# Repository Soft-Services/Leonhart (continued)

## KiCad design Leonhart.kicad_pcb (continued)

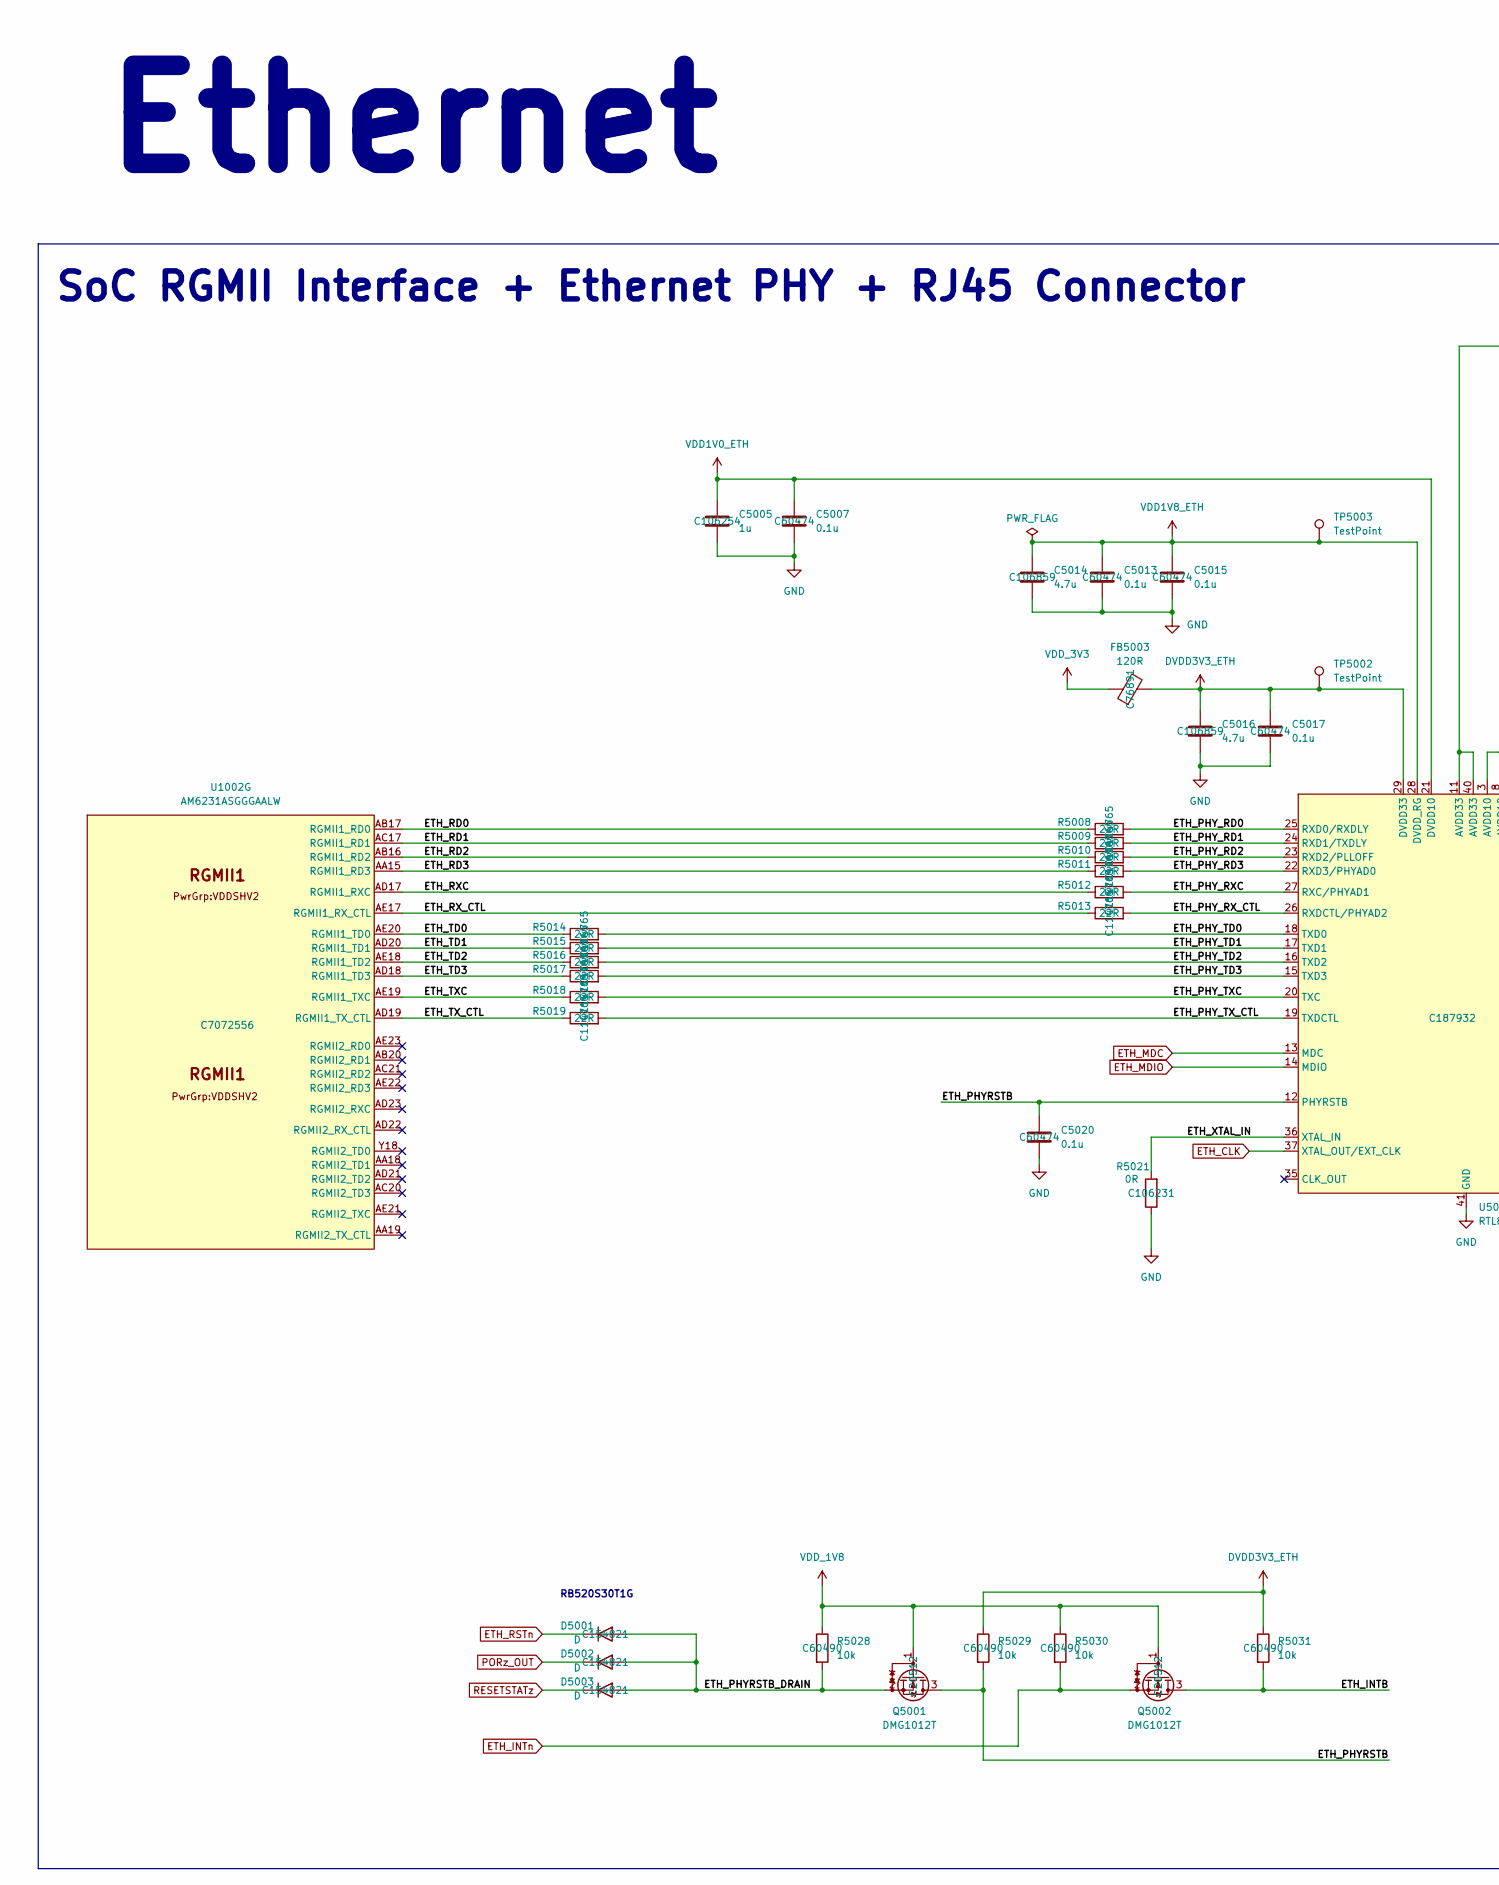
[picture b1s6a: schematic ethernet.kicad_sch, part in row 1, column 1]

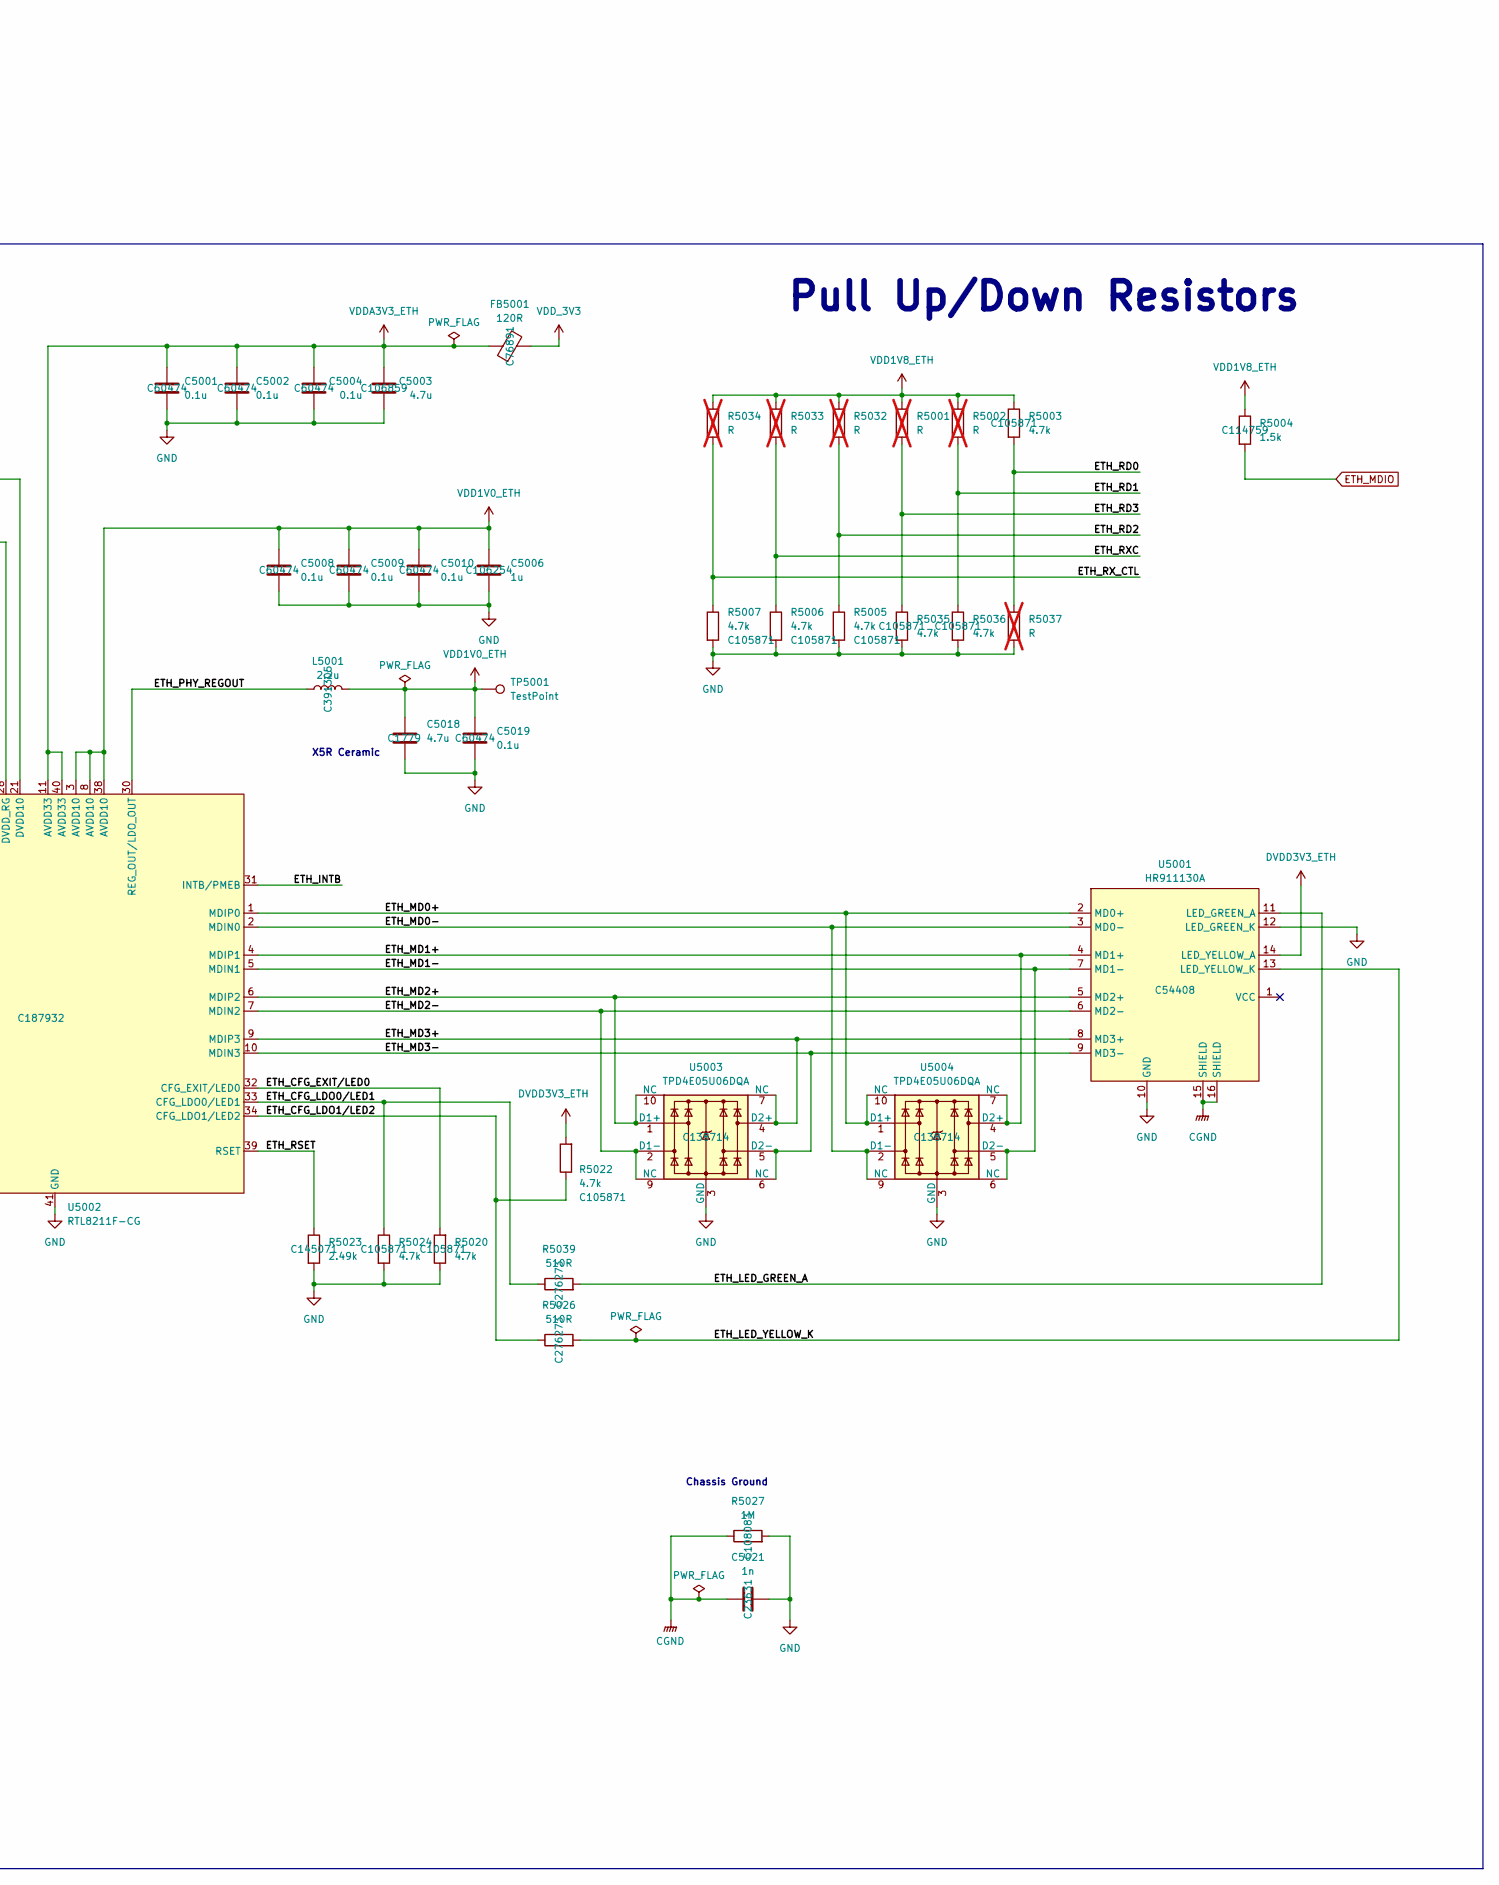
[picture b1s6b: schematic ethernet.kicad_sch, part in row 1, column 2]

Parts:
C5001, C5002, C5004, C5007, C5008, C5009, C5010, C5013, C5015, C5017, C5019, C5020: 0.1u; C_0402_1005Metric; JLCPCB Part# C60474
C5003, C5014, C5016: 4.7u; C_0402_1005Metric; JLCPCB Part# C106859
C5005, C5006: 1u; C_0402_1005Metric; JLCPCB Part# C106254
C5018: 4.7u; C_0805_2012Metric; JLCPCB Part# C1779
C5021: 1n; C_1206_3216Metric; JLCPCB Part# C23631
D5001, D5002, D5003: D; D_SOD-523; JLCPCB Part# C154821
FB5001, FB5003: 120R; R_0402_1005Metric; JLCPCB Part# C76891
L5001: 2.2u; DFE2HCAH1R0MJ0L; JLCPCB Part# C391305
Q5001, Q5002: DMG1012T; SOT-523; JLCPCB Part# C20512
R5001, R5002, R5032, R5033, R5034, R5037: R; R_0402_1005Metric; not fitted
R5003, R5005, R5006, R5007, R5020, R5022, R5024, R5035, R5036: 4.7k; R_0402_1005Metric; JLCPCB Part# C105871
R5004: 1.5k; R_0402_1005Metric; JLCPCB Part# C114759
R5008, R5009, R5010, R5011, R5012, R5013, R5014, R5015, R5016, R5017, R5018, R5019: 22R; R_0402_1005Metric; JLCPCB Part# C114765
R5021: 0R; R_0402_1005Metric; JLCPCB Part# C106231
R5023: 2.49k; R_0402_1005Metric; JLCPCB Part# C145071
R5026, R5039: 510R; R_0402_1005Metric; JLCPCB Part# C276273
R5027: 1M; R_0402_1005Metric; JLCPCB Part# C108083
R5028, R5029, R5030, R5031: 10k; R_0402_1005Metric; JLCPCB Part# C60490
TP5001, TP5002, TP5003: TestPoint; TestPoint_Pad_1.0x1.0mm
U1002: AM6231ASGGGAALW; BGA425C50P25X25_1300X1300X89; JLCPCB Part# C7072556
U5001: HR911130A; JLCPCB Part# C54408
U5002: RTL8211F-CG; QFN-40-1EP_5x5mm_P0.4mm_EP3.6x3.6mm; JLCPCB Part# C187932
U5003, U5004: TPD4E05U06DQA; USON-10_2.5x1.0mm_P0.5mm; JLCPCB Part# C138714

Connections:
/Ethernet [5]/ETH_CFG_EXIT/LED0: R5020.2, U5002.32 (CFG_EXIT/LED0)
/Ethernet [5]/ETH_CFG_LDO0/LED1: R5024.1, R5039.1, U5002.33 (CFG_LDO0/LED1)
/Ethernet [5]/ETH_CFG_LDO1/LED2: R5022.1, R5026.1, U5002.34 (CFG_LDO1/LED2)
/Ethernet [5]/ETH_INTB: Q5002.3 (D), R5031.2, U5002.31 (INTB/PMEB)
/Ethernet [5]/ETH_LED_GREEN_A: R5039.2, U5001.11 (LED_GREEN_A)
/Ethernet [5]/ETH_LED_YELLOW_K: R5026.2, U5001.13 (LED_YELLOW_K)
/Ethernet [5]/ETH_MD0+: U5001.2 (MD0+), U5002.1 (MDIP0), U5004.1 (D1+), U5004.10 (NC)
/Ethernet [5]/ETH_MD0-: U5001.3 (MD0-), U5002.2 (MDIN0), U5004.2 (D1-), U5004.9 (NC)
/Ethernet [5]/ETH_MD1+: U5001.4 (MD1+), U5002.4 (MDIP1), U5004.4 (D2+), U5004.7 (NC)
/Ethernet [5]/ETH_MD1-: U5001.7 (MD1-), U5002.5 (MDIN1), U5004.5 (D2-), U5004.6 (NC)
/Ethernet [5]/ETH_MD2+: U5001.5 (MD2+), U5002.6 (MDIP2), U5003.1 (D1+), U5003.10 (NC)
/Ethernet [5]/ETH_MD2-: U5001.6 (MD2-), U5002.7 (MDIN2), U5003.2 (D1-), U5003.9 (NC)
/Ethernet [5]/ETH_MD3+: U5001.8 (MD3+), U5002.9 (MDIP3), U5003.4 (D2+), U5003.7 (NC)
/Ethernet [5]/ETH_MD3-: U5001.9 (MD3-), U5002.10 (MDIN3), U5003.5 (D2-), U5003.6 (NC)
/Ethernet [5]/ETH_PHYRSTB: C5020.1, Q5001.3 (D), R5029.2, U5002.12 (PHYRSTB)
/Ethernet [5]/ETH_PHYRSTB_DRAIN: D5001.2 (A), D5002.2 (A), D5003.2 (A), Q5001.2 (S), R5028.2
/Ethernet [5]/ETH_PHY_RD0: R5008.2, U5002.25 (RXD0/RXDLY)
/Ethernet [5]/ETH_PHY_RD1: R5009.2, U5002.24 (RXD1/TXDLY)
/Ethernet [5]/ETH_PHY_RD2: R5010.2, U5002.23 (RXD2/PLLOFF)
/Ethernet [5]/ETH_PHY_RD3: R5011.2, U5002.22 (RXD3/PHYAD0)
/Ethernet [5]/ETH_PHY_REGOUT: L5001.1, U5002.30 (REG_OUT/LDO_OUT)
/Ethernet [5]/ETH_PHY_RXC: R5012.2, U5002.27 (RXC/PHYAD1)
/Ethernet [5]/ETH_PHY_RX_CTL: R5013.2, U5002.26 (RXDCTL/PHYAD2)
/Ethernet [5]/ETH_PHY_TD0: R5014.2, U5002.18 (TXD0)
/Ethernet [5]/ETH_PHY_TD1: R5015.2, U5002.17 (TXD1)
/Ethernet [5]/ETH_PHY_TD2: R5016.2, U5002.16 (TXD2)
/Ethernet [5]/ETH_PHY_TD3: R5017.2, U5002.15 (TXD3)
/Ethernet [5]/ETH_PHY_TXC: R5018.2, U5002.20 (TXC)
/Ethernet [5]/ETH_PHY_TX_CTL: R5019.2, U5002.19 (TXDCTL)
/Ethernet [5]/ETH_RD0: R5003.2, R5008.1, R5037.1, U1002.AB17 (RGMII1_RD0)
/Ethernet [5]/ETH_RD1: R5002.2, R5009.1, R5036.1, U1002.AC17 (RGMII1_RD1)
/Ethernet [5]/ETH_RD2: R5005.1, R5010.1, R5032.2, U1002.AB16 (RGMII1_RD2)
/Ethernet [5]/ETH_RD3: R5001.2, R5011.1, R5035.1, U1002.AA15 (RGMII1_RD3)
/Ethernet [5]/ETH_RSET: R5023.1, U5002.39 (RSET)
/Ethernet [5]/ETH_RXC: R5006.1, R5012.1, R5033.2, U1002.AD17 (RGMII1_RXC)
/Ethernet [5]/ETH_RX_CTL: R5007.1, R5013.1, R5034.2, U1002.AE17 (RGMII1_RX_CTL)
/Ethernet [5]/ETH_TD0: R5014.1, U1002.AE20 (RGMII1_TD0)
/Ethernet [5]/ETH_TD1: R5015.1, U1002.AD20 (RGMII1_TD1)
/Ethernet [5]/ETH_TD2: R5016.1, U1002.AE18 (RGMII1_TD2)
/Ethernet [5]/ETH_TD3: R5017.1, U1002.AD18 (RGMII1_TD3)
/Ethernet [5]/ETH_TXC: R5018.1, U1002.AE19 (RGMII1_TXC)
/Ethernet [5]/ETH_TX_CTL: R5019.1, U1002.AD19 (RGMII1_TX_CTL)
/Ethernet [5]/ETH_XTAL_IN: R5021.2, U5002.36 (XTAL_IN)
CGND: C5021.1, R5027.1, U5001.15 (SHIELD), U5001.16 (SHIELD)
DVDD3V3_ETH: C5016.1, C5017.1, FB5003.2, R5022.2, R5029.1, R5031.1, TP5002.1, U5001.14 (LED_YELLOW_A), U5002.29 (DVDD33); also elsewhere on the board
ETH_CLK: U5002.37 (XTAL_OUT/EXT_CLK); also elsewhere on the board
ETH_INTn: Q5002.2 (S), R5030.2; also elsewhere on the board
ETH_MDC: U5002.13 (MDC); also elsewhere on the board
ETH_MDIO: R5004.2, U5002.14 (MDIO); also elsewhere on the board
ETH_RSTn: D5001.1 (K); also elsewhere on the board
GND: C5001.2, C5002.2, C5003.2, C5004.2, C5005.2, C5006.2, C5007.2, C5008.2, C5009.2, C5010.2, C5013.2, C5014.2, C5015.2, C5016.2, C5017.2, C5018.2, C5019.2, C5020.2, C5021.2, R5005.2, R5006.2, R5007.2, R5020.1, R5021.1, R5023.2, R5024.2, R5027.2, R5035.2, R5036.2, R5037.2, U5001.10 (GND), U5001.12 (LED_GREEN_K), U5002.41 (GND), U5003.3 (GND), U5003.8 (GND), U5004.3 (GND), U5004.8 (GND); also elsewhere on the board
PORz_OUT: D5002.1 (K); also elsewhere on the board
RESETSTATz: D5003.1 (K); also elsewhere on the board
VDD1V0_ETH: C5005.1, C5006.1, C5007.1, C5008.1, C5009.1, C5010.1, C5018.1, C5019.1, L5001.2, TP5001.1, U5002.3 (AVDD10), U5002.8 (AVDD10), U5002.21 (DVDD10), U5002.38 (AVDD10); also elsewhere on the board
VDD1V8_ETH: C5013.1, C5014.1, C5015.1, R5001.1, R5002.1, R5003.1, R5004.1, R5032.1, R5033.1, R5034.1, TP5003.1, U5002.28 (DVDD_RG); also elsewhere on the board
VDDA3V3_ETH: C5001.1, C5002.1, C5003.1, C5004.1, FB5001.1, U5002.11 (AVDD33), U5002.40 (AVDD33)
VDD_1V8: Q5001.1 (G), Q5002.1 (G), R5028.1, R5030.1; also elsewhere on the board
VDD_3V3: FB5001.2, FB5003.1; also elsewhere on the board

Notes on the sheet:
X5R Ceramic
Pull Up/Down Resistors
RB520S30T1G
SoC RGMII Interface + Ethernet PHY + RJ45 Connector
Chassis Ground
Ethernet

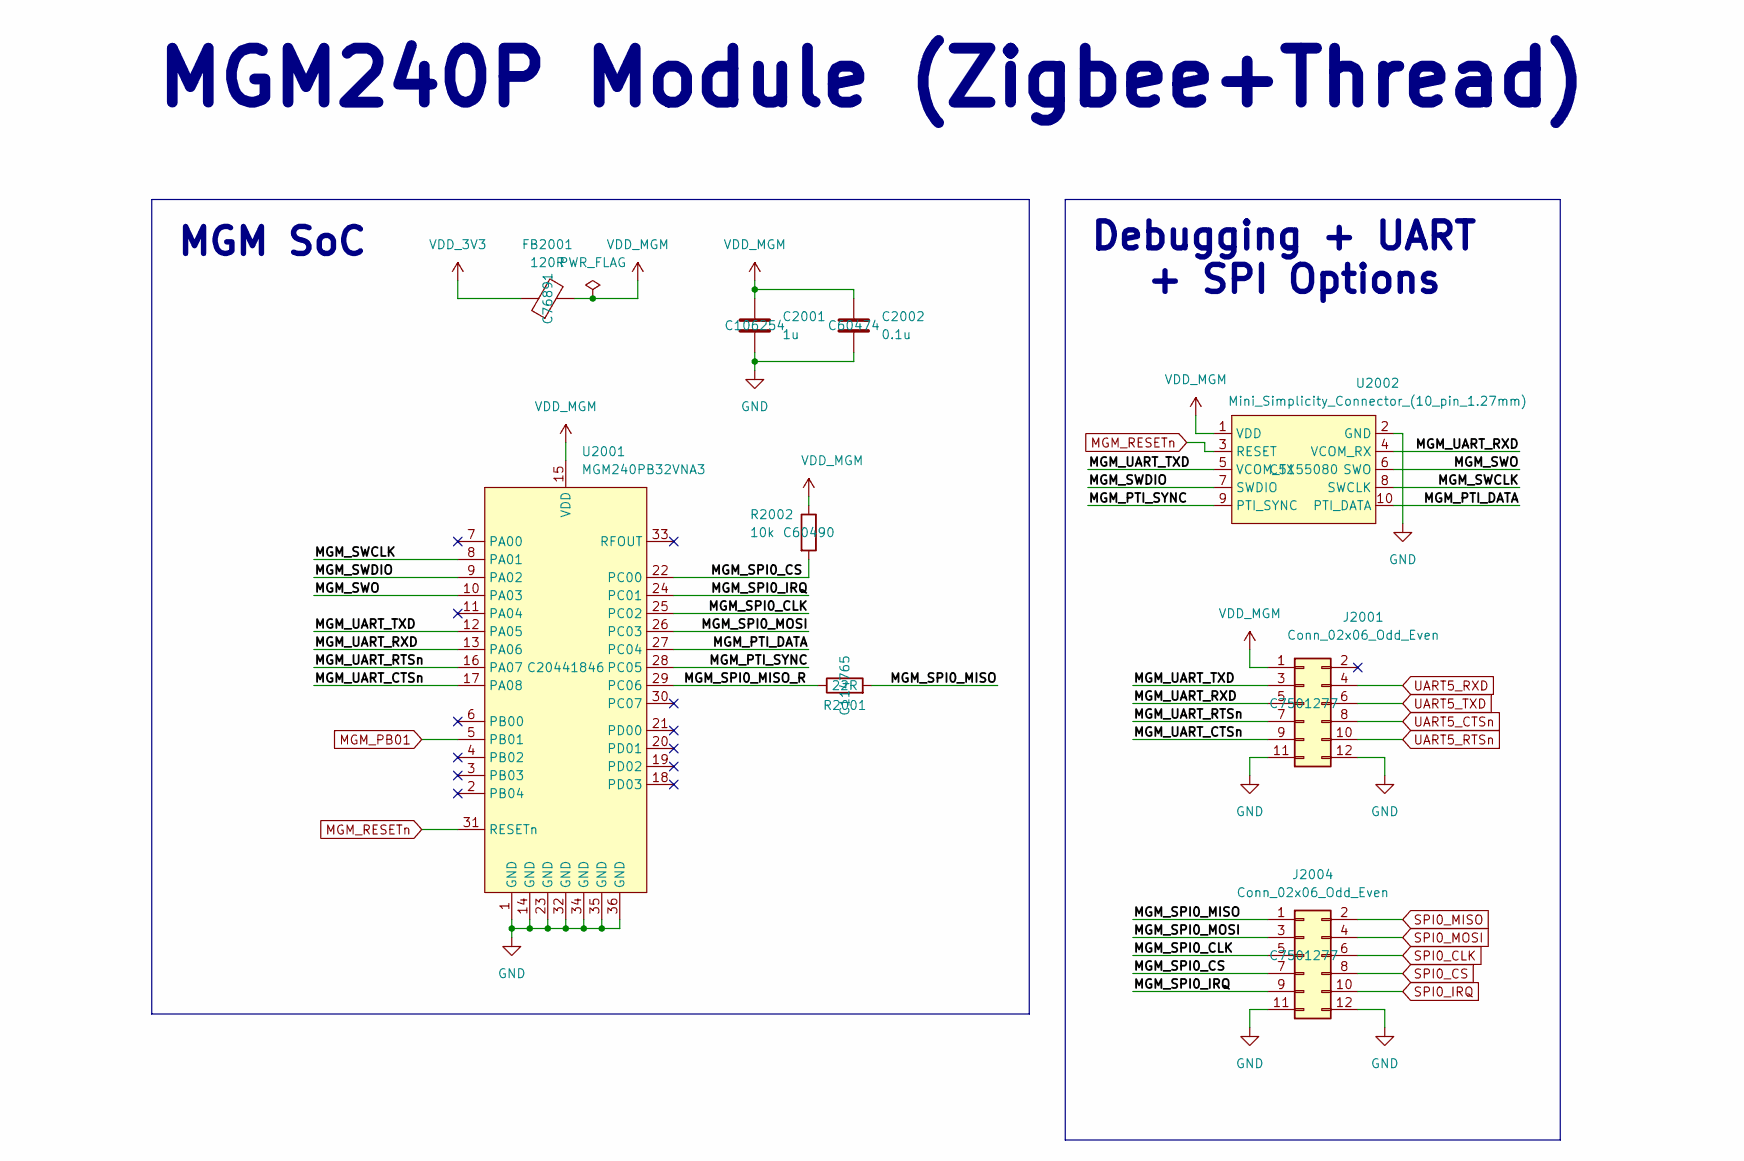
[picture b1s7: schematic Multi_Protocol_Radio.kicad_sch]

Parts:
C2001: 1u; C_0402_1005Metric; JLCPCB Part# C106254
C2002: 0.1u; C_0402_1005Metric; JLCPCB Part# C60474
FB2001: 120R; R_0402_1005Metric; JLCPCB Part# C76891
J2001, J2004: Conn_02x06_Odd_Even; PinHeader_2x06_P2.54mm_Vertical; JLCPCB Part# C7501277
R2001: 22R; R_0402_1005Metric; JLCPCB Part# C114765
R2002: 10k; R_0402_1005Metric; JLCPCB Part# C60490
U2001: MGM240PB32VNA3; JLCPCB Part# C20441846
U2002: Mini_Simplicity_Connector_(10_pin_1.27mm); FTSH10501LDVK; JLCPCB Part# C5155080

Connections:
/Zigbee+Thread [2]/MGM_PTI_DATA: U2001.27 (PC04), U2002.10 (PTI_DATA)
/Zigbee+Thread [2]/MGM_PTI_SYNC: U2001.28 (PC05), U2002.9 (PTI_SYNC)
/Zigbee+Thread [2]/MGM_SPI0_CLK: J2004.5, U2001.25 (PC02)
/Zigbee+Thread [2]/MGM_SPI0_CS: J2004.7, R2002.2, U2001.22 (PC00)
/Zigbee+Thread [2]/MGM_SPI0_IRQ: J2004.9, U2001.24 (PC01)
/Zigbee+Thread [2]/MGM_SPI0_MISO: J2004.1, R2001.2
/Zigbee+Thread [2]/MGM_SPI0_MISO_R: R2001.1, U2001.29 (PC06)
/Zigbee+Thread [2]/MGM_SPI0_MOSI: J2004.3, U2001.26 (PC03)
/Zigbee+Thread [2]/MGM_SWCLK: U2001.8 (PA01), U2002.8 (SWCLK)
/Zigbee+Thread [2]/MGM_SWDIO: U2001.9 (PA02), U2002.7 (SWDIO)
/Zigbee+Thread [2]/MGM_SWO: U2001.10 (PA03), U2002.6 (SWO)
/Zigbee+Thread [2]/MGM_UART_CTSn: J2001.9, U2001.17 (PA08)
/Zigbee+Thread [2]/MGM_UART_RTSn: J2001.7, U2001.16 (PA07)
/Zigbee+Thread [2]/MGM_UART_RXD: J2001.5, U2001.13 (PA06), U2002.4 (VCOM_RX)
/Zigbee+Thread [2]/MGM_UART_TXD: J2001.3, U2001.12 (PA05), U2002.5 (VCOM_TX)
GND: C2001.2, C2002.2, J2001.11, J2001.12, J2004.11, J2004.12, U2001.1 (GND), U2001.14 (GND), U2001.23 (GND), U2001.32 (GND), U2001.34 (GND), U2001.35 (GND), U2001.36 (GND), U2002.2 (GND); also elsewhere on the board
MGM_PB01: U2001.5 (PB01); also elsewhere on the board
MGM_RESETn: U2001.31 (RESETn), U2002.3 (RESET); also elsewhere on the board
SPI0_CLK: J2004.6; also elsewhere on the board
SPI0_CS: J2004.8; also elsewhere on the board
SPI0_IRQ: J2004.10; also elsewhere on the board
SPI0_MISO: J2004.2; also elsewhere on the board
SPI0_MOSI: J2004.4; also elsewhere on the board
UART5_CTSn: J2001.8; also elsewhere on the board
UART5_RTSn: J2001.10; also elsewhere on the board
UART5_RXD: J2001.4; also elsewhere on the board
UART5_TXD: J2001.6; also elsewhere on the board
VDD_3V3: FB2001.1; also elsewhere on the board
VDD_MGM: C2001.1, C2002.1, FB2001.2, J2001.1, R2002.1, U2001.15 (VDD), U2002.1 (VDD)

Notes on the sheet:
Debugging + UART + SPI Options
MGM SoC
MGM240P Module (Zigbee+Thread)
